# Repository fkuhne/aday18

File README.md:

# aday18
Material utilizado durante as minhas palestras no Arduino Day 2018 da PUCRS.

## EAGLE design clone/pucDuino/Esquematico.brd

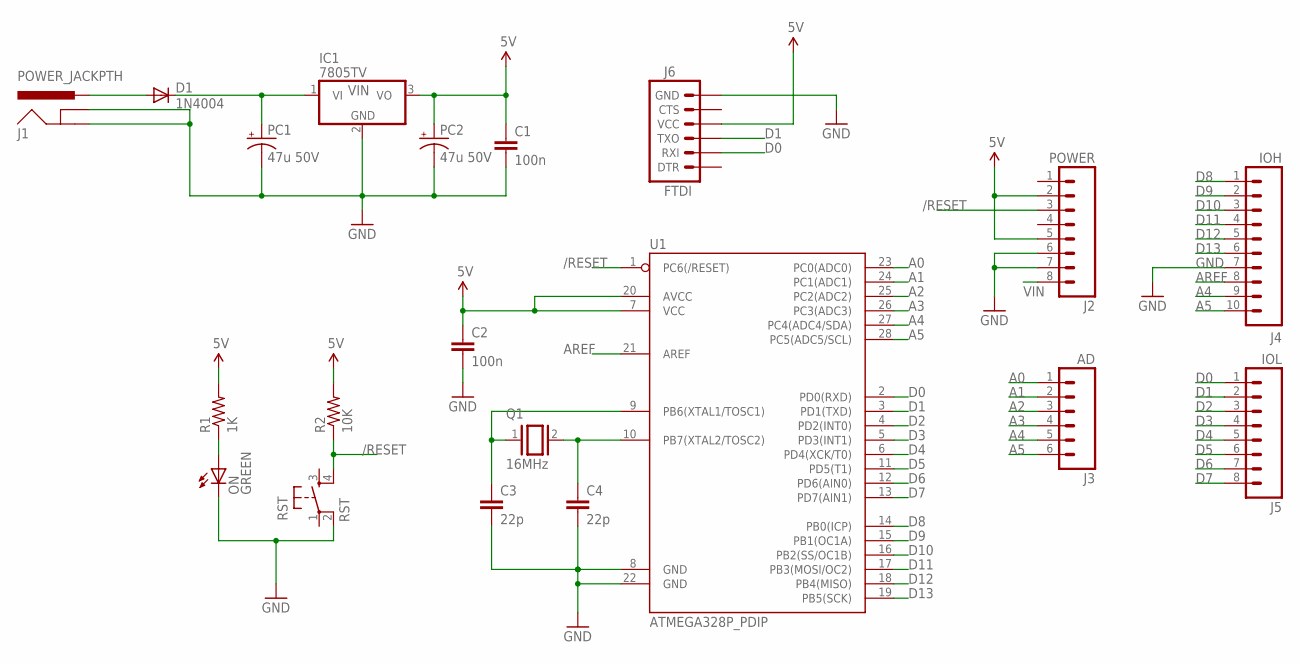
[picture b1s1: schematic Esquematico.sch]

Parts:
C1: 100n; C2.5-3
C2: 100n; CAP-PTH-SMALLEZ
C3, C4: 22p; CAP-PTH-SMALLEZ
D1: 1N4004; DO41-10
IC1: 7805TV; TO220V
J1: POWER_JACKPTH; POWER_JACK_PTH
J2: POWER; 1X08_PIN1_NO_SILK
J3: AD; 1X06_NO_SILK
J4: IOH; 1X10_NO_SILK
J5: IOL; 1X08_PIN1_NO_SILK
J6: FTDI; 1X06
ON: GREEN; LED3MM
PC1, PC2: 47u 50V; TAP5-50
Q1: 16MHz; QS
R1: 1K; AXIAL-0.3
R2: 10K; AXIAL-0.3
RST: RST; TAC-SWITCH-PTH
U1: ATMEGA328P_PDIP; DIL28-3

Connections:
5V: C1.1, C2.1, IC1.3 (VO), J2.2, J2.5, J6.4 (VCC), PC2.+, R1.P$2 (2), R2.P$2 (2), U1.7 (VCC), U1.20 (AVCC)
/RESET: J2.3, R2.P$1 (1), RST.4, U1.1 (PC6(/RESET))
A0: J3.1, U1.23 (PC0(ADC0))
A1: J3.2, U1.24 (PC1(ADC1))
A2: J3.3, U1.25 (PC2(ADC2))
A3: J3.4, U1.26 (PC3(ADC3))
A4: J3.5, J4.9, U1.27 (PC4(ADC4/SDA))
A5: J3.6, J4.10, U1.28 (PC5(ADC5/SCL))
AREF: J4.8, U1.21 (AREF)
D0: J5.1, J6.2 (RXI), U1.2 (PD0(RXD))
D1: J5.2, J6.3 (TXO), U1.3 (PD1(TXD))
D2: J5.3, U1.4 (PD2(INT0))
D3: J5.4, U1.5 (PD3(INT1))
D4: J5.5, U1.6 (PD4(XCK/T0))
D5: J5.6, U1.11 (PD5(T1))
D6: J5.7, U1.12 (PD6(AIN0))
D7: J5.8, U1.13 (PD7(AIN1))
D8: J4.1, U1.14 (PB0(ICP))
D9: J4.2, U1.15 (PB1(OC1A))
D10: J4.3, U1.16 (PB2(SS/OC1B))
D11: J4.4, U1.17 (PB3(MOSI/OC2))
D12: J4.5, U1.18 (PB4(MISO))
D13: J4.6, U1.19 (PB5(SCK))
GND: C1.2, C2.2, C3.2, C4.2, IC1.2 (GND), J1.GND, J1.GNDBREAK, J2.6, J2.7, J4.7, J6.6 (GND), ON.K (C), PC1.-, PC2.-, RST.2, U1.8 (GND), U1.22 (GND)
unnamed: C4.1, Q1.2, U1.10 (PB7(XTAL2/TOSC2))
unnamed: ON.A, R1.P$1 (1)
unnamed: D1.A, J1.PWR
VIN: D1.C, IC1.1 (VI), J2.8, PC1.+
XTAL1: C3.1, Q1.1, U1.9 (PB6(XTAL1/TOSC1))

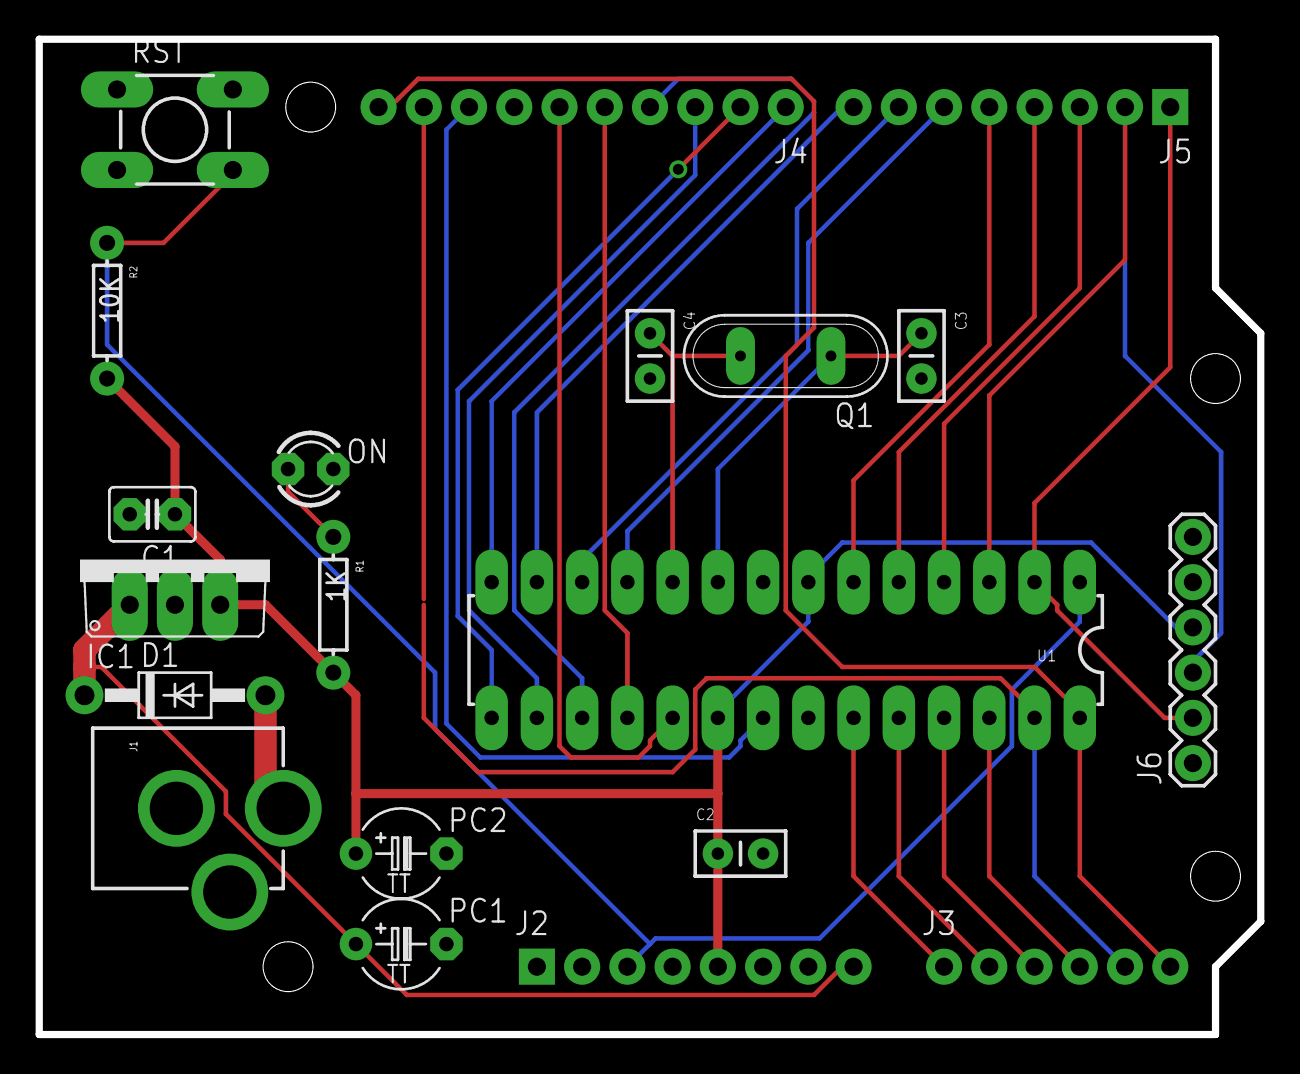
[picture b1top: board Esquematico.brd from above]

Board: 2 copper layers, 68.6 x 55.9 mm, 20 parts (0 on the bottom side), 29 nets.

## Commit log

2018-05-06 Adicionando primeiros arquivos da palestra de introducao.
2018-05-07 Criando slides...
2018-05-09 Atuaizando...
2018-05-09 Digamos que está pronto...
2018-05-09 Esta parece ser a versão final.
2018-05-10 Adicionando slides e roteiro.
2018-05-11 Removendo arquivos desnecessários.
2018-05-11 Adicionando placas e slide com placas.
2018-05-11 Incluindo slides e circuitos.
2018-05-12 Ultima versão.
2018-05-12 Atualizando a placa do Arduino.
2018-05-12 Atualizando e adicionando PDF.
2018-05-12 Adicionando todos os arquivos, organizadamente.

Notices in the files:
parts and their libraries:
SparkFun-DigitalIC: Licensing: Creative Commons ShareAlike 4.0 International - https://creativecommons.org/licenses/by-sa/4.0
